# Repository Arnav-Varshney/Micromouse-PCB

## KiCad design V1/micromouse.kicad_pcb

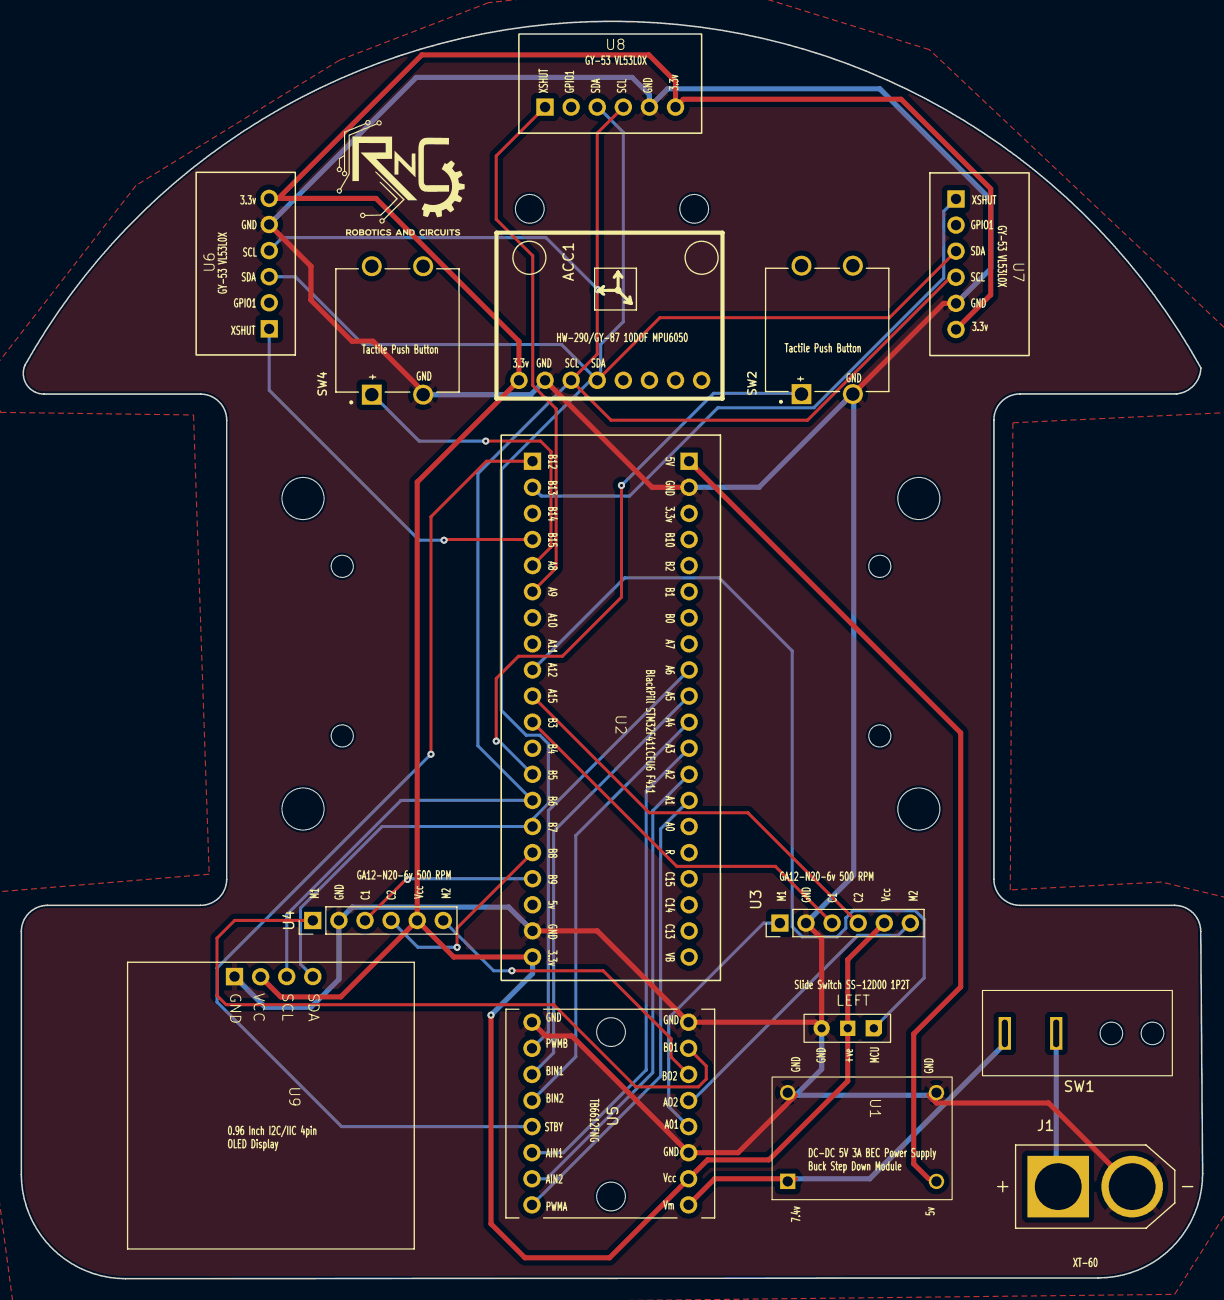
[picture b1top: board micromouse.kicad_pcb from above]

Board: 2 copper layers, 115.0 x 122.4 mm, 15 parts (0 on the bottom side), 28 nets.

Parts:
ACC1: GY-521; GY-521_SMD
J1: XT60-M; AMASS_XT60-M
SW1: SW_SPST; battery_sw
SW2, SW4: SW_Push; SW_VS-1213-67-160GF
SW3: SW_SPDT_312; SLIDE SW
U1: BUCK; buck
U2: STM32 Blackpill; STM32
U3: N20 encoder right; PinHeader_1x06_P2.54mm_Vertical
U4: N20 encoder left; PinHeader_1x06_P2.54mm_Vertical
U5: TB6612FNG
U6: VL53L0X left; VL53L0X
U7: VL53L0X right; VL53L0X
U8: VL53L0X middle; VL53L0X
U9: oled i2c; oled

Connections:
3.3v: ACC1.1 (VCC), SW3.2 (C), U2.20 (3V3), U3.5 (vcc), U4.5 (vcc), U5.2 (VCC), U6.1 (Vin), U7.1 (Vin), U8.1 (Vin), U9.2 (VCC)
5v: U1.2 (OUT+), U2.40 (5V)
7.4v: J1.P (POS), SW1.1 (A)
7.4vb: SW1.2 (B), U1.1 (IN+), U5.1 (VM)
AIN1: U2.29 (A3), U5.14 (AI1)
AIN2: U2.28 (A2), U5.15 (AI2)
AO1: U3.1 (motor_1), U5.4 (A01)
AO2: U3.6 (motor_2), U5.5 (A02)
BIN1: U2.30 (A4), U5.12 (BI1)
BIN2: U2.31 (A5), U5.11 (BI2)
BO1: U4.1 (motor_1), U5.7 (B01)
BO2: U4.6 (motor_2), U5.6 (B02)
GND: ACC1.2 (GND), J1.N (NEG), SW2.2, SW3.3 (A), SW4.2, U1.3 (IN-), U1.4 (OUT-), U2.19 (GND), U2.39 (GND), U3.2 (gnd), U4.2 (gnd), U5.3 (GND), U5.8 (GND), U5.9 (GND), U6.2 (GND), U7.2 (GND), U8.2 (GND), U9.1 (GND)
PWM A: U2.27 (A1), U5.16 (PWMA)
PWM B: U2.32 (A6), U5.10 (PWMB)
SCL: ACC1.3 (SCL), U2.14 (B6), U6.3 (SCL), U7.3 (SCL), U8.3 (SCL), U9.3 (SCL)
SDA: ACC1.4 (SDA), U2.15 (B7), U6.4 (SDA), U7.4 (SDA), U8.4 (SDA), U9.4 (SDA)
STBY: U2.1 (B12), U5.13 (STBY)
XSHUT 1: U2.2 (B13), U7.6 (~XSHUT)
XSHUT 2: U2.6 (A9), U8.6 (~XSHUT)
XSHUT 3: U2.4 (B15), U6.6 (~XSHUT)
encoder A1: U2.11 (B3), U3.3 (c1)
encoder A2: U2.17 (B9), U4.3 (c1)
encoder B1: U2.10 (A15), U3.4 (c2)
encoder B2: U2.16 (B8), U4.4 (c2)
push button: SW4.1, U2.5 (A8)
push button 1: SW2.1, U2.13 (B5)
slide_SW: SW3.1 (B), U2.9 (A12)

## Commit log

2025-02-13 symbol addition
2025-02-13 STM32 symbol addition
2025-02-13 mpu6050 encoder motor symbol
2025-02-13 structure change
2025-02-14 schematic
2025-02-14 schematic changes v1
2025-02-14 schematic changes
2025-02-14 TB6612FNG footprints
2025-02-15 footprints
2025-02-15 footprint changes
2025-02-15 push button and buck footprint
2025-02-16 schematic changes, and footprint assignment
2025-02-16 schematic and footprint changes
2025-02-16 routing
2025-02-18 pcb changes
2025-02-18 oled
2025-02-19 cost excel
2025-02-20 routing 1
2025-02-21 final routing
2025-02-22 3d models
2025-02-22 pcb changes!!!!!
2025-03-21 final
2025-04-15 hello world
2025-04-15 hello
2025-04-18 added uart
2025-04-22 v2 start
2025-04-22 v3 addition
